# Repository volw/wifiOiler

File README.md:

# wifiOiler

Automatischer streckenabhängiger Kettenöler für's Motorrad mit folgenden Funktionen:

- Ermittlung der zurückgelegten Strecke per GPS.
- Auslösen eines Ölvorgangs nach einer einstellbaren Anzahl von Metern.
- Drei verschiedene Distanzen oder Modi einstellbar (Normal, Regen, Offroad). 
- Notlaufprogramm = zeitabhängiges Ölen, falls kein GPS Signal empfangen werden kann.
- Bedienung über Button, Feedback per zweifarbiger LED.
- Erweiterte Bedienung über jedes internetfähige Gerät, auf dem ein Internet Browser läuft, z.B. Handy, Notebook, etc..
- Der Öler kann sich in ein bestehendes WLAN einklinken oder selber einen Access Point erstellen.
- WiFi kann jederzeit an- oder ausgestellt werden (während der Fahrt wird WiFi automatisch abgeschaltet).
- Aufzeichnung der gefahrenen Strecken im Speicher (LittleFS-Dateisystem) des verwendeten ESP8266 Chips (Platz für ca. 45 Stunden Fahrzeit vorhanden).
- Übertragen (und löschen) der aufgezeichneten Strecken per WLAN auf einen zentralen Web-Server (s. Oilerbase auf Basis eines Raspberry Pis, Strecken können auch manuell heruntergeladen werden).
- Herunterladen von Updates von einem zentralen Web-Server (s. Oilerbase). Updates können auch per Upload ausgelöst werden.
- PHP Skripte und html Dateien für den zentralen Web-Server (Apache auf Raspberry Pi, s. Oilerbase)
- Software zur Konvertierung der aufgezeichneten Tracks in das .gpx Format (können dann z.B. auf Google Earth angezeigt werden).

In diesem Repo zu finden:

- Schaltplan und Teileliste zur Erstellung und Bestückung der Platine.
- Vorschläge für Bauteile zum Einbau in das Motorrad.
- Komplette Software für Öler, Oilerbase und Track Konvertierung.
- Anleitungen für Aufbau, Inbetriebnahme und Bedienung (s. "docs").
- Einbauvorschlag.

Wem das alles zuviel an Bastelei ist und Hilfe bei Erstellung der Platine, bzw. Steuereinheit benötigt, kann sich gerne melden...

## Credits

Detlev Axon, creator of [RehOiler](https://www.rehtronik.de/startseite1.html)

Mikal Hart, creator of [TinyGPS++](https://github.com/mikalhart/TinyGPSPlus), an NMEA parsing library.

Hristo Gochkov for the FSBrowser example.

Maarten Lamers for his distance calculation (taken from TinyGPS++)

Patrick Gillespie for his [Macro Font Generator](http://patorjk.com/software/taag).

And many thanks to all the others who share their knowledge

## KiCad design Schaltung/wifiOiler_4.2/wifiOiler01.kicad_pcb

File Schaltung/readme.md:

# Schaltung

Die Schaltung wurde zuletzt mit KiCad 5.1.9_1 bearbeitet. Alle Symbole und Footprints wurden lokal verlinkt und sind in den Verzeichnissen enthalten (Symbole in wifiOilerLib.lib, Footprints in ProjectFootprints.pretty).

Abstände und Leiterbahnen wurden großzügig ausgelegt, um Fräsen und Löten zu erleichtern.

Noch ist eine Leiterbahn auf der zweiten Seite vorhanden, die aber auch noch eliminiert werden kann, wenn die Leiterbahnen, die zum Displayanschluss führen, etwas umgeroutet werden. Für eine Auftragsfertigung ist es fast egal, ob ein- oder zweiseitig, da viele Fertiger einseitige Platinen gar nicht mehr anbieten. Möchte man die Platine selber fräsen, sollte sie natürlich einseitig sein. Hier die Änderung, die dazu notwendig wäre (oben die aktuelle Ansicht, darunter die Änderung)

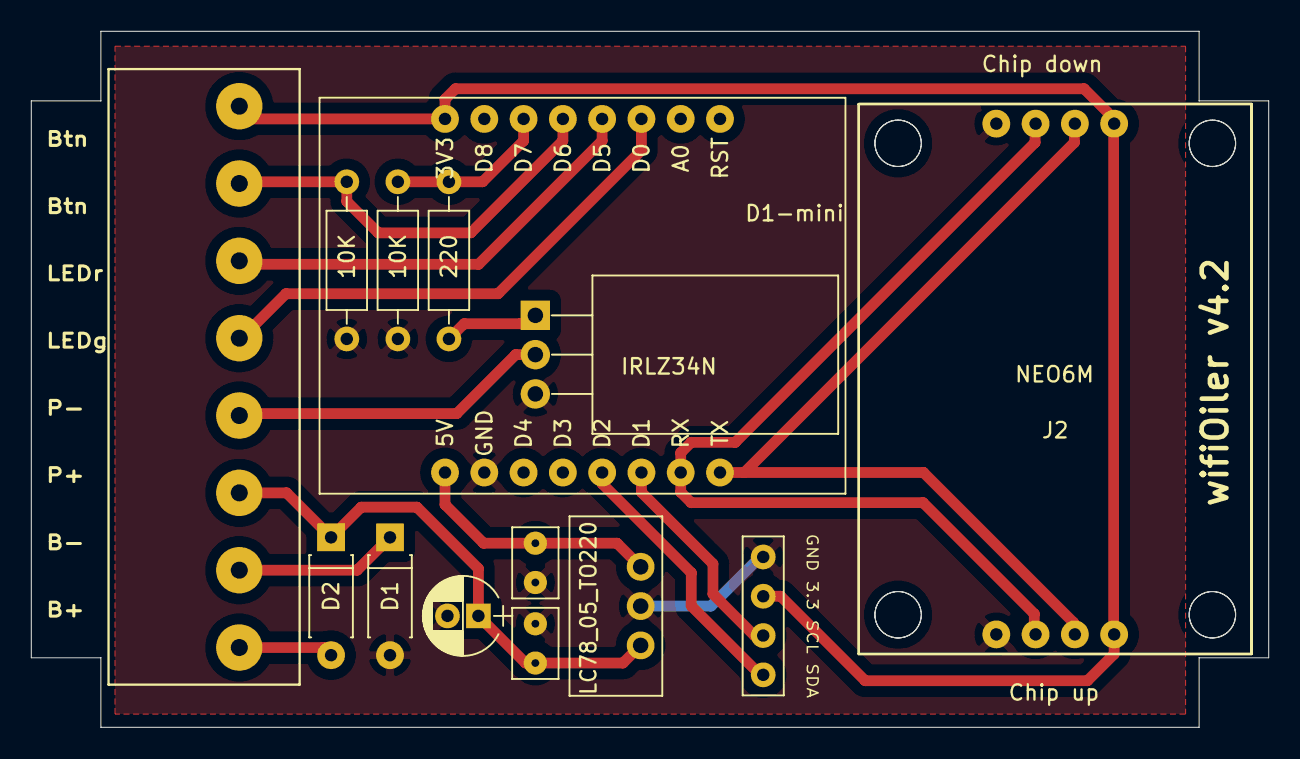
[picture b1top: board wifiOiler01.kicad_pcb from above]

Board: 2 copper layers, 80.0 x 45.0 mm, 15 parts (0 on the bottom side), 16 nets.

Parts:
C1, C2: CP_Small; MKS02-63 100N Folienkondensator
C3: 10 uF; CP_Radial_D5.0mm_P2.00mm
D1, D2: 1N4004; D_DO-41_SOD81_P7.62mm_Horizontal
J1: Conn_01x04; Pin_Header_Straight_1x04_Pitch2.54mm
J2: Conn_01x04; NEO6M_18_ChipUp
MCU1: D1-mini; D1 mini (ESP8266)
N1: NEO6M; NEO6M_18_ChipDown
P1: CONN_01X08; Stiftleiste_1x8_5mm_D13_Box_korr
Q1: IRLZ34N; TO-220-3_Horizontal_NoPad
R1: 220; R_Axial_DIN0207_L6.3mm_D2.5mm_P10.16mm_Horizontal
R2, R3: 10K; R_Axial_DIN0207_L6.3mm_D2.5mm_P10.16mm_Horizontal
U1: LC78_05_TO220; LC78_0.5 aufrecht

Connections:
unnamed: C1.1, MCU1.16, U1.3
unnamed: C1.2, C2.2, C3.2, D1.2, J1.4, J2.4, MCU1.15, N1.4, Q1.3, R2.2, R3.2, U1.2
unnamed: C2.1, C3.1, D2.1, P1.3, U1.1
unnamed: D1.1, P1.2
unnamed: D2.2, P1.1
unnamed: J1.1, MCU1.12
unnamed: J1.2, MCU1.11
unnamed: J1.3, J2.1, MCU1.8, N1.1, P1.8
unnamed: J2.2, MCU1.9, N1.2
unnamed: J2.3, MCU1.10, N1.3
unnamed: MCU1.3, P1.5
unnamed: MCU1.4, P1.6
unnamed: MCU1.5, P1.7, R3.1
unnamed: MCU1.6, R1.1, R2.1
unnamed: P1.4, Q1.2
unnamed: Q1.1, R1.2

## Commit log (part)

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2021-01-28 4.2.011 minor corrections
2021-01-28 gpsTrack update
2021-01-29 doku gpstrack
2021-01-29 Renamed global vars for better identification
2021-01-29 working at the docs
2021-02-02 serve connecttest.txt and hotspot-detect.html inline
2021-02-02 redundant pinmode / remove delays
2021-02-02 just typo
2021-02-02 extending docs
2021-02-02 optimized start procedure
2021-02-02 called code parts too often
2021-02-02 License added
2021-02-02 License stuff
2021-02-02 redundant setUserAgent() removed
2021-02-03 extracting messages
2021-02-03 docs
2021-02-03 updating php scripts
2021-02-03 some corrections
2021-02-04 Einbau Beispiel
2021-02-04 code restructured
2021-02-05 messages extracted to messages include
2021-02-07 Update progress bar/%/totals
2021-02-18 Doku erweitert
2021-02-18 checkFileSystemSpace & messages
2021-02-18 kurzes Einbaubeispiel AT + pics
2021-02-18 Schaltung
2021-02-18 image link fixed
2021-02-18 Schaltung readme updated
2021-02-19 docs updated
2021-02-19 display lib changed
2021-02-19 lib dependencies in docs fixed
2021-02-19 minor display lib changes (defines)
2021-02-19 FSBrowser function in docs
2021-02-19 Clarify fsbrowser save function
2021-02-19 changed MCU to SoC
2021-02-19 Schaltung readme.md completed (nothing more to say)
2021-02-19 resizing embedded pictures
2021-02-22 timeout optimized
2021-02-22 fixed delay in mode permanent
2021-02-22 delayed start of LED response
2021-02-22 enthalten...
2021-02-22 fixed links
2021-02-22 Neo-6M photo
2021-02-22 don't blame ...
2021-03-01 moved changelog from wifiOiler.h
2021-03-09 remove configureGPS
2021-03-09 configure GPS
    provide config files for different GPS modules including configuration procedure. Need seperate serial for this?
2021-03-09 working at the docs...
2021-03-15 pump & led test, file list with size
2021-03-17 config page
2021-03-18 FSbrowser- and reboot- services
2021-03-18 global text defines
2021-03-30 gps config removed
2021-03-30 config param gps config file in source
2021-04-01 4.2.014, minor corrections
2021-04-07 runtime info - pump mode bug
2021-04-15 Initial Load
2021-04-15 remove old phps
2021-04-16 4.2.016: some corrections
    - modified config.htm (menu after save)
    - adjust message (GPS Initialisation)
    - double buffer size (update upload)
    - messages file upload (update)
2021-04-20 4.2.017: remove index.html
2021-04-20 working...
    impl. conf. param "bac" for user credentials (user:password). credentials will be passed to oiler as base64 encoded string and is decoded for config.html
2021-04-29 #defined messages in upload.ino
2021-05-27 Header Bug uploading tracks
    printf("...\n") was used -> use \r\n instead -> printf("...\r\n")
    otherwise apache will report 400 error (parsing header)
    spend 4 hours with debugging (during corona - so don't mind)
2021-05-28 4.2.018 bug fix parsing update info
2021-05-28 4.2.019 message fix
2021-05-31 4.2.019 bug in getUpdateInfo() (wrong handling for empty result)
2021-06-30 cosmetic changes
2021-08-03 docu bug
2021-08-03 4.2.021: fixed movement bug (Issue #6)
    moved movement check to trigger function (where it belongs ;-)
2021-08-03 4.2.022: delete large log file
    check file size of log file when starting - delete, if exceeded
2021-08-03 small opt
2021-08-04 messages opt.
    ..and eliminated some compiler warnings (just for fun)
2021-08-04 file upload: too many line feeds at end of transfer
2021-08-04 gpsTrack: read loop condition
    ...and removed not required using directives
2021-08-04 wrong title
2021-08-04 gpsTrack: added fixpoint count
2021-08-16 Update upload.ino
    multiple checks if file arrived. Check was sometimes faster than moving uploaded file from temp to original location (apache/php - only with bigger files?)...
2021-08-30 image
2021-08-30 typo
2022-08-16 Update link
2022-08-18 GPS Track Filename Prefix
2022-08-18 gpsTrack updated (prefix)
2022-08-23 deleting debug messages
    changed label in config.htm and oiler.ini (gts)
2022-08-24 4.2.024 checking options
2022-08-24 upload.htm an allgemeinen Look angepasst
2022-09-12 config updated
2022-09-13 upload updated
2022-09-14 Update 4.2.025
    Track Upload Fixed (http response 400 & 499 on nginx)
    Save _all_ config params in oiler.ini (not only already saved params)
2022-09-14 pumpmode page updated
2022-09-15 updated board #defines
2022-09-17 Links updated
2022-09-22 Update Copyright Note
2022-10-12 adjust to local timezone (tbc)
    convert utc timestamps from gps to local time
2023-02-15 optimize wifi
2023-02-16 shutdown wifi before reboot
    Beim Wechsel von WLAN auf Access Point konnte regelmäßig kein Access Point beim ersten Start erstellt werden
2023-02-19 wifi opt
2023-02-19 add raw html data
2023-02-20 shrink script
2023-02-20 html messagebox
    when captive portal is used no javascript::alert() will work (at least on my iphone) - changed to html message box
2023-02-23 Remove fs-browser option
    choose fs-browser html with define FS_BROWSER_URL
2023-02-23 4.2.027 removed fsbrowser option
    is a #define now
2023-02-28 update fix
2023-03-02 switch to Update.writeStream()
2023-03-03 update define for pro
2023-03-03 board type in runtime info
2023-03-03 bt info docs
2023-03-03 Display feedback while updating
2023-03-05 basic auth doc
2023-03-05 minor corrections
2023-03-06 html message & confirm
2023-03-06 html compressed
2023-03-06 index.htm updated
2023-03-06 html message, confirm
2023-03-06 ValueList corr, http error (isServerAvailable())
2023-03-08 css extended
2023-03-08 FileSystemBrowser extended
    added messages and spinner for async operations
2023-03-08 more message for file system browser...
2023-03-08 somewhat compressed
2023-03-09 config load/save spinner
2023-03-09 info load spinner
2023-03-09 input to buttons
2023-03-09 input -> button (binary)
2023-03-13 4.2.029 response improvements
    added spinner - less messages, (c) update, html validated
2023-03-14 changed styles (new theme)
2023-03-17 finetuning (fsbrowser, message)
2023-03-20 display zipped content (don't edit)
2023-03-21 info page: styles updated
2023-03-21 styles update
2023-03-21 html binaries
2023-03-21 remove inline style download frame
2023-03-21 correct url (removed unnecessary parameter)
2023-03-21 binaries updated
2023-03-21 fsbrowser: copy function
2023-03-21 4.2.030 copy function added
2023-03-22 show progress on file upload
2023-03-22 zip symbol in browser
2023-03-22 re-evented browser
2023-03-23 update config
2023-03-23 update info
2023-03-23 force list load on save after extract
2023-03-23 clean up
2023-03-23 check xhr.status in onload, added _NO_OLD_FILES_
2023-03-27 don't save non text files
2023-04-20 minor updates on webhandler
2023-05-09 help text in ini file
2023-06-06 some messages & start delay
2023-06-07 not yet completed...
2023-06-17 last moves to printf macros
2023-06-17 new config
2023-06-28 Log file rotation
2023-06-28 update check in main loop
2023-06-29 HTML check for uploaded firmware
    check for uploaded firmware in fsbrowser
    new webhandler for /checkupd
    bool reboot in checkforUpdate not needed
2023-06-29 version update
2023-07-10 minor changes
2023-07-13 help note
2023-07-13 make logger static, move printf macros to logger
2023-08-18 seconds between track points fix
2024-08-19 update copyright notice
2025-03-25 detail message connect error
    404 message in isServerAvailable()
